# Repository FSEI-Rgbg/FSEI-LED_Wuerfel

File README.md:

# FSEI - LED Würfel - Lötübung

Dieses Projekt wurde als Lötübung ins Leben gerufen. Es handelt sich um eine kleine Platine mit 7 LEDs und einem Taster. Beim Drücken des Tasters wird eine Zahl zwischen 1 und 6 gewürfelt, wie bei einem echten Würfel auch.

## Wie sieht denn der Würfel eigentlich aus?
Bei einem solchen Projekt darf natürlich der FSEIgel nicht fehlen. Er hat selbstverständlich seinen ganz eigenen Platz auf der Platine bekommen.<p>
<p>
<p>
<p>
Eine [interaktive BOM](https://htmlpreview.github.io/?https://github.com/FSEI-Rgbg/FSEI-LED_Wuerfel/blob/main/Hardware%20-%20KiCAD/KiCAD-Project/bom/FSEI_WuerfelPlatine_v2.0.html) zur einfachen Komponentenplatzierung gibt's natürlich auch.

## Projekt Status
Der Würfel ist voll funktionsfähig und als Lötübung in der Fachschaft Elektro- und Informationstechnik als Kit mit allen benötigten Komponenten sowie bereits installierter Software erhältlich.

Still ToDo:
- Version 2.0 ist (Stand 02.07.2023) noch UNTESTED!
- Dokumentation
- Bilder von KIT hinzufügen

## Zielgruppe / Dauer
<p> Diese Lötübung zielt auf alle Elektro- und Lötbegeisterten, oder die die es noch werden möchten, ab einem Alter von etwa 12-14 Jahren ab.
<p>Mit ein wenig handwerklichem Geschick kann nach etwa 30-45 Minuten losgewürfelt werden.

## Kit
**TODO** - _Bild folgt!_
<br>
<p>Der Würfel wird mit allen benötigten Bauteilen in einer kleinen Box herausgegeben. Enthalten ist alles, von der Platine, über die Batterie bis hin zu den LEDs.
<p>Wenn es für dich möglich ist, würden wir dich bitten, die Box nach erfolgreichem Zusammenbau wieder bei uns abzugeben.
<p>Danke für deine Mithilfe.

## Dokumentation
**TODO**
<br>
Eine Dokumentation wie alles funktioniert, zusammengebaut werden muss inkl. einer kurzen Erklärung für alles Weitere findest du [hier](/Doku/Dokumentation-FSEI-LED_Wuerfel_v2.0.pdf).<p>
Der interaktive Bestückungsplan ist [hier](https://htmlpreview.github.io/?https://github.com/FSEI-Rgbg/FSEI-LED_Wuerfel/blob/main/Hardware%20-%20KiCAD/KiCAD-Project/bom/FSEI_WuerfelPlatine_v2.0.html) zu finden. Damit kannst du einfach der Reihe nach alle Komponenten einbauen und Stück für Stück abhaken, was du schon erledigt hast.

## Support
Bei Problemen, Fragen oder Anregungen bitte einfach bei der Fachschaft Elektro- und Informationstechnik (S060) melden.

## Software
**TODO**
<br>
Beim Drücken des Tasters wird ein Timer gestartet, außerdem startet eine Würfelanimation. Beim Loslassen des Tasters wird eine Zufallszahl gewürfelt, dargestellt und nach etwa 7 Sekunden wieder ausgeschalten. Durch die gedrückte Zeit des Tasters ergibt sich hierbei die Zufälligkeit. <p>
Weitere Details findest du in der [Dokumentation](#Dokumentation) oder im [Programmcode](/Software/Code/).

## Hardware
<p>Die Version 1.0 des Würfels wurde mit Hilfe von EasyEDA erstellt. Die Version 2.0 der Platine enthält einige Verbesserungen des ursprünglichen Designs und wurde in KiCAD realisiert.
<p>Im Mittelpunkt der Platine steht neben unserem FSEIgel natürlich ein kleiner Computer, ein sogenannter Mikroprozessor. Wir haben uns hierbei für den ATtiny13A von Atmel entschieden.

## Technische Daten / Stromverbrauch
- Stromaufnahme bei 3V: <p>
Modus  &  Stromaufnahme <p>
0,088 uA  @  Tiefschlafmodus <p>
0,9 mA  @  0 LEDs, CPU Idle <p>
1,808 mA  @  1 LED, CPU Idle <p>
10,8 mA  @  6 LEDs, CPU Idle

- Maße: 60 x 35 x ~10 mm

- Verwendungszweck: Würfel für Spieleabende

## Ich habe einen Bug gefunden oder eine Verbesserung
[Siehe Support](#Support)

## Wir sind ein Verein oder Gruppe von Studenten und wollen mehrere Bausätze kaufen
Es ist toll, dass du anderen Zeigen möchtest wie einfach Löten oder Elektrotechnik sein kann. Melde dich bei uns.

## Autoren
- Leo Scherer
- Patrick Lermer

## Inspired by
BlinkyParts
- https://github.com/Binary-Kitchen/SolderingTutorial
- https://binary-kitchen.github.io/SolderingTutorial/
- https://shop.blinkyparts.com/de/Bausaetze/

## Copyright and Authorship
[CC-BY-SA 4.0](https://creativecommons.org/licenses/by-sa/4.0/) - Fachschaft Elektro- und Informationstechnik der OTH Regensburg

[© FSEI OTH Regensburg](https://www.fsei-regensburg.de)

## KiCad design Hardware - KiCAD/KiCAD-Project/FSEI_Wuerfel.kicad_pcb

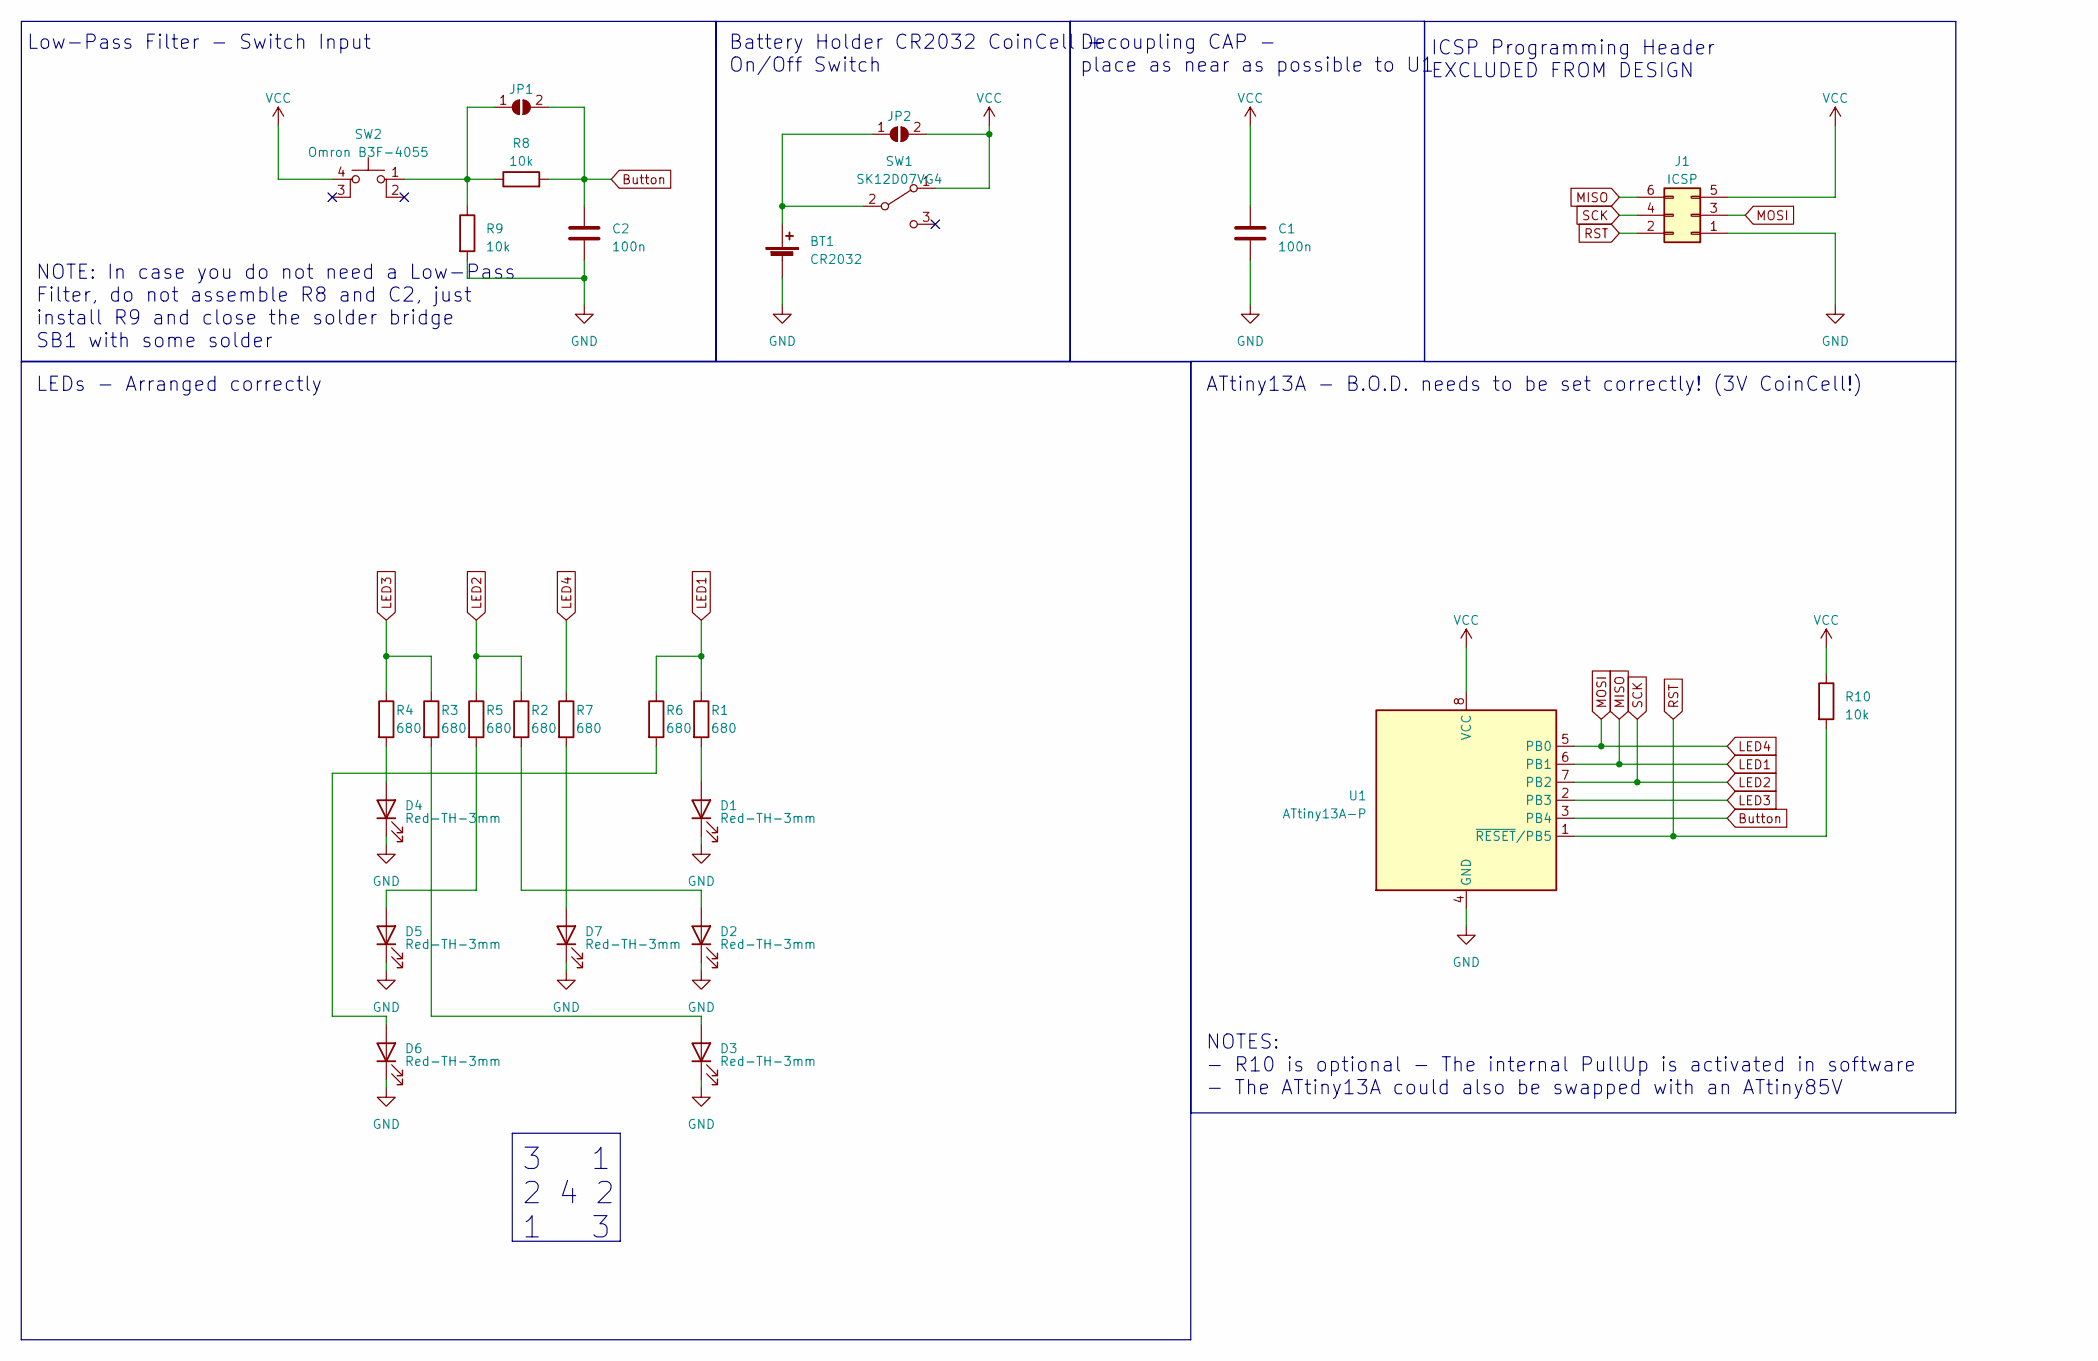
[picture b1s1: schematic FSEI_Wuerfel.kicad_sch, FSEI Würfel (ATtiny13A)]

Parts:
BT1: CR2032; BAT-TH_BS-2-1
C1, C2: 100n; C_Disc_D3.0mm_W1.6mm_P2.50mm
D1, D2, D3, D4, D5, D6, D7: Red-TH-3mm; LED_D3.0mm
J1: ICSP; PinSocket_2x03_P2.54mm_Vertical
JP1, JP2: SolderJumper_2_Open; SolderJumper-2_P1.3mm_Open_RoundedPad1.0x1.5mm
R1, R2, R3, R4, R5, R6, R7: 680; R_Axial_DIN0207_L6.3mm_D2.5mm_P10.16mm_Horizontal
R8, R9, R10: 10k; R_Axial_DIN0207_L6.3mm_D2.5mm_P10.16mm_Horizontal
SW1: SK12D07VG4; SW-TH_SK12D07VG4
SW2: Omron B3F-4055; KEY-TH_4P-L12.0-W12.0-P5.00-LS13.4-EH
U1: ATtiny13A-P; DIP-8_W7.62mm

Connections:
Button: C2.1, JP1.2 (B), R8.2, U1.3 (PB4)
GND: BT1.2 (-), C1.2, C2.2, D1.1 (K), D2.1 (K), D3.1 (K), D4.1 (K), D5.1 (K), D6.1 (K), D7.1 (K), J1.1, R9.2, U1.4 (GND)
LED1: J1.6, R1.1, R6.1, U1.6 (PB1)
LED2: J1.4, R2.1, R5.1, U1.7 (PB2)
LED3: R3.1, R4.1, U1.2 (PB3)
LED4: J1.3, R7.1, U1.5 (PB0)
unnamed: BT1.1 (+), JP2.1 (A), SW1.2 (B)
unnamed: D1.2 (A), R1.2
unnamed: D2.2 (A), R2.2
unnamed: D3.2 (A), R3.2
unnamed: D4.2 (A), R4.2
unnamed: D5.2 (A), R5.2
unnamed: D6.2 (A), R6.2
unnamed: D7.2 (A), R7.2
unnamed: JP1.1 (A), R8.1, R9.1, SW2.1
RST: J1.2, R10.2, U1.1 (~RESET/PB5)
VCC: C1.1, J1.5, JP2.2 (B), R10.1, SW1.1 (A), SW2.4 (A), U1.8 (VCC)

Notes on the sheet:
3 1 2 4 2 1 3
ICSP Programming Header EXCLUDED FROM DESIGN
NOTE: In case you do not need a Low-Pass Filter, do not assemble R8 and C2, just install R9 and close the solder bridge SB1 with some solder
Decoupling CAP - place as near as possible to U1
Low-Pass Filter - Switch Input
NOTES: - R10 is optional - The internal PullUp is activated in software - The ATtiny13A could also be swapped with an ATtiny85V
ATtiny13A - B.O.D. needs to be set correctly! (3V CoinCell!)
Battery Holder CR2032 CoinCell + On/Off Switch
LEDs - Arranged correctly

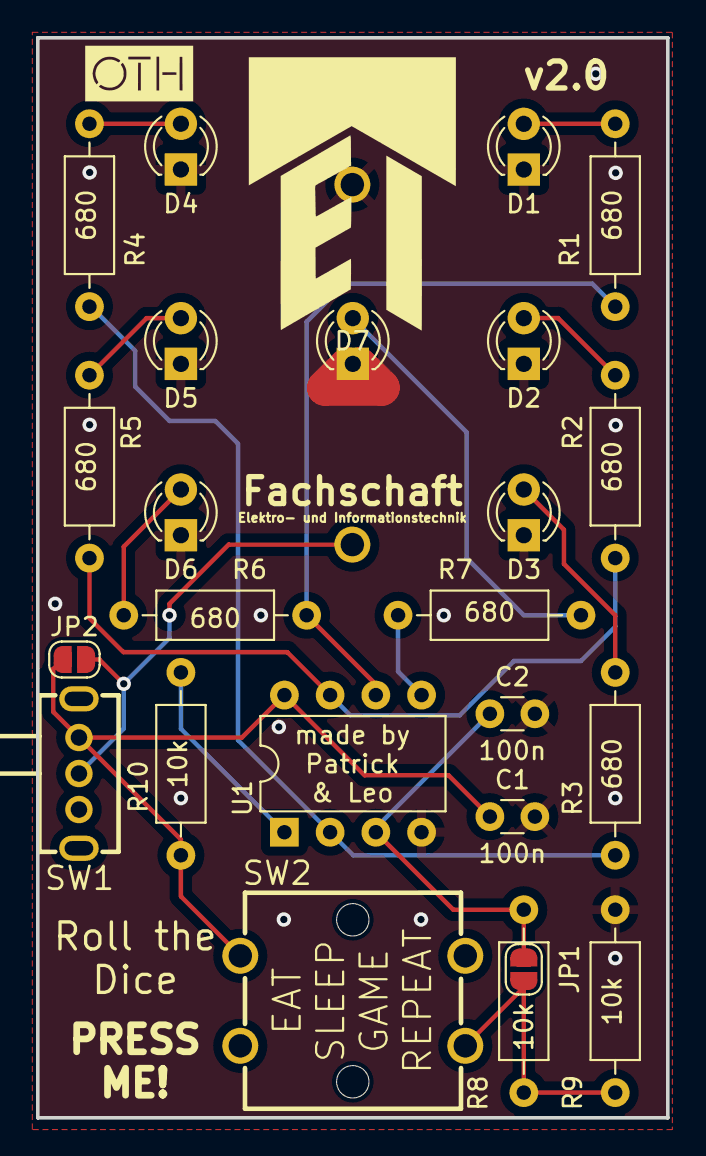
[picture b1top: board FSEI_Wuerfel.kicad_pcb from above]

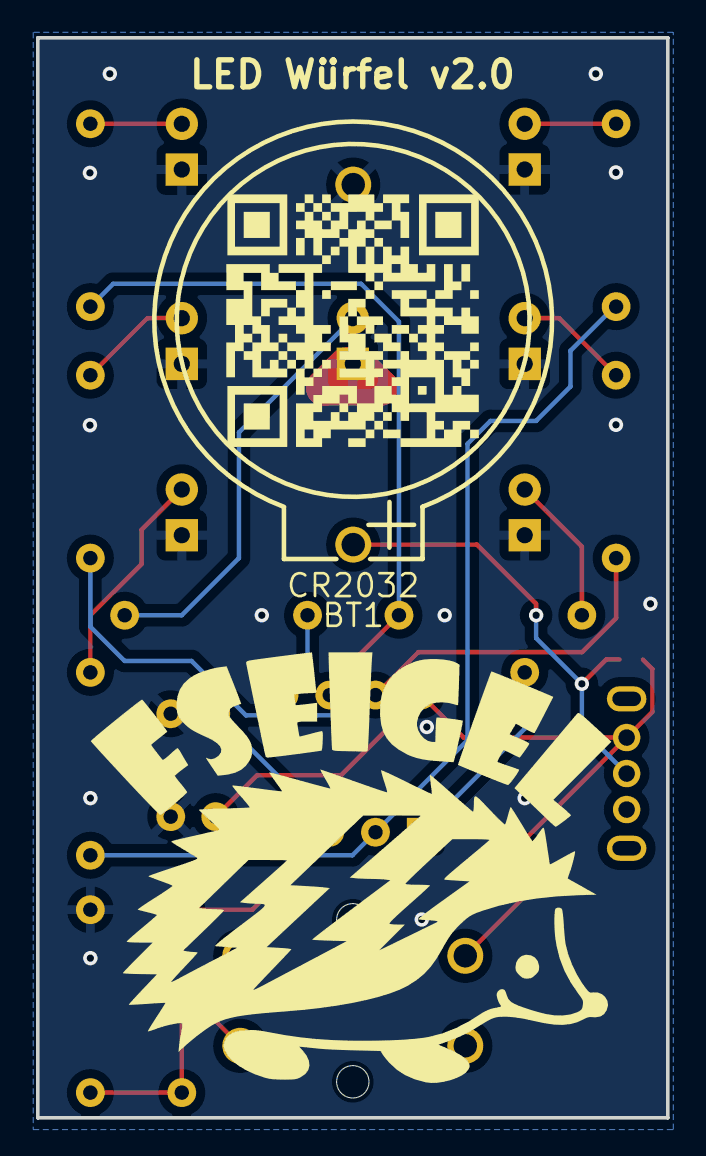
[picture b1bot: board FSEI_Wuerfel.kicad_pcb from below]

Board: 2 copper layers, 35.0 x 60.0 mm, 30 parts (3 on the bottom side), 17 nets.

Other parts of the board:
G01, G02, G011, G012, G100: LOGO

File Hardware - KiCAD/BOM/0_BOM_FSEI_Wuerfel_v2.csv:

"Source:","C:\Users\Patrick\OneDrive\Dokumente\FSEI\FSEI-LED_Wuerfel\Hardware - KiCAD\KiCAD-Project\FSEI_Wuerfel.kicad_sch"
"Date:","6/22/2023 8:53:04 AM"
"Tool:","Eeschema 7.0.2"
"Generator:","C:\Program Files\KiCad\7.0\bin\scripting\plugins/bom_csv_grouped_by_value_with_fp.py"
"Component Count:","25"
"Ref","Qnty","Value","Cmp name","Footprint","Description","Vendor","DNP"
"BT1","1","CR2032","Battery_Cell","C70376:BAT-TH_BS-2-1","Single-cell battery","",""
"C1, C2","2","100n","C","Capacitor_THT:C_Disc_D3.0mm_W1.6mm_P2.50mm","Unpolarized capacitor","",""
"D1, D2, D3, D4, D5, D6, D7","7","Red-TH-3mm","LED","LED_THT:LED_D3.0mm","Light emitting diode","",""
"JP1, JP2","2","SolderJumper_2_Open","SolderJumper_2_Open","Jumper:SolderJumper-2_P1.3mm_Open_RoundedPad1.0x1.5mm","Solder Jumper, 2-pole, open","",""
"R1, R2, R3, R4, R5, R6, R7","7","680","R","Resistor_THT:R_Axial_DIN0207_L6.3mm_D2.5mm_P10.16mm_Horizontal","Resistor","",""
"R8, R9, R10","3","10k","R","Resistor_THT:R_Axial_DIN0207_L6.3mm_D2.5mm_P10.16mm_Horizontal","Resistor","",""
"SW1","1","SK12D07VG4","SW_SPDT","C393937:SW-TH_SK12D07VG4","Switch, single pole double throw","",""
"SW2","1","Omron B3F-4055","SW_MEC_5E","C84931:KEY-TH_4P-L12.0-W12.0-P5.00-LS13.4-EH","MEC 5E single pole normally-open tactile switch","",""
"U1","1","ATtiny13A-P","ATtiny13A-P","Package_DIP:DIP-8_W7.62mm","20MHz, 1kB Flash, 64B SRAM, 64B EEPROM, debugWIRE, DIP-8","",""

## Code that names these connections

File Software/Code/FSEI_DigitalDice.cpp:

/*
Fachschaft Elektro- & Informationstechnik, OTH Regensburg, ©2023

Digitaler Würfel - Lötübung
ATtiny13A oder ATtiny85V

Inputs:    
    Taster mit PullDown und LowPassFilter an PB4 (Pin 3) - Interrupt PCINT4

Outputs:   
    LED Gruppen:
        LED1 = PB1 (Pin 6)
        LED2 = PB2 (Pin 7)
        LED3 = PB3 (Pin 2)
        LED4 = PB0 (Pin 5)
    ┌───┐   ┌───┐
    │ 3 │   │ 1 │
    ├───┼───┼───┤
    │ 2 │ 4 │ 2 │
    ├───┼───┼───┤
    │ 1 │   │ 3 │
    └───┘   └───┘

Funktionsprinzip:
    uC geht direkt in Tiefschlafmodus um Strom zu sparen.
    Sobald der Taster gedrückt wird, aktiviert sich der Timer (der mit 9,6MHz zählt), 
    und zählt endlos nach oben und läuft über. Die CPU ist dabei Idle.
    Sobald der Taster losgelassen wird, wird per XOR und Modulo aus dem Wert des Timers die anzuzeigende Zahl bestimmt.
    Dann wird der Interrupt des Timers aktiviert, welcher den TIMER_COUNTER solange hochzählt, 
    bis etwa 7s vergangen sind. Dann wird alles deaktiviert und wieder in den Tiefschlafmodus versetzt.

Stromaufnahme bei 3V:
    Tiefschlafmodus:    0,088 uA
    0 LEDs, CPU Idle:     0,9 mA
    1 LED, CPU Idle:    1,808 mA
    6 LEDs, CPU Idle:    10,8 mA
*/

// Einbinden aller benötigten Bibliotheken (Zusatzfunktionen)
#include <avr/io.h>
#include <avr/interrupt.h>
#include <avr/sleep.h>

// Timer Modus für das Warten auf Abschaltung, dadurch hat er einen hohen Prescaler und wenig Interrupts.
#define TMODE_IDLE 0
// Timer Modus für das Ermitteln einer Zufallszahl, dafür wird die höchste Auflösung und kein Prescaler benötigt.
#define TMODE_TRNG 1


// Zusätzlicher Zähler, um den Timer auf 24-Bit zu erweitern.
volatile unsigned short TIMER_COUNTER = 0;
// Timer Modus Variable, die den derzeitigen Zustand speichert.
volatile unsigned char TIMER_USAGE_MODE = 0;
// Zähler für das Durchlaufen aller Würfelzustände
volatile unsigned char DICE_ANIM_COUNTER = 0;
// Speicher für den vorherigen Würfel-Wurf.
volatile unsigned char PREV_DICE_ROLL = 0;


// Ausgabe der gewürfelten Augenzahl auf LEDs. Rest von PORTB bleibt unverändert.
void DisplayAugenzahl(unsigned char Zahl)     
{
    // Alle LEDs deaktivieren
    PORTB &= ~((1 << PORTB3) | (1 << PORTB2) | (1 << PORTB1) | (1 << PORTB0));

    switch (Zahl)
    {
        case 1: //LED4
            PORTB |= (1 << PORTB0);
        break;

        case 2: // LED1
            PORTB |= (1 << PORTB1);
            break;

        case 3: // LED1 & LED4
            PORTB |= ((1 << PORTB1) | (1 << PORTB0));
            break;

        case 4: // LED1 & LED3
            PORTB |= ((1 << PORTB1) | (1 << PORTB3));
            break;

        case 5: // LED1 & LED3 & LED4
            PORTB |= ((1 << PORTB1) | (1 << PORTB3) | (1 << PORTB0));
            break;

        case 6: // LED1 & LED2 & LED3
            PORTB |= ((1 << PORTB1) | (1 << PORTB2) | (1 << PORTB3));
            break;

        default: 
            break;
    }
}


// Timer im jeweiligen Modus aktivieren und mit einem festgelegten Wert starten.
void activate_timer(unsigned char timer_mode, unsigned char timer_value)
{
    TCCR0B = 0x00;                              // Timer stoppen falls er schon läuft.
    TIMER_USAGE_MODE = timer_mode;              // Timer Modus für Interrupt Routine speichern.
    TIMER_COUNTER = 0;                          // Zusätzlichen Timer Counter zurücksetzen.
    TCNT0 = timer_value;                        // Timer Wert setzen.

    TIMSK0 = (1 << TOIE0);                      // Timer-Interrupt anschalten.

    switch (timer_mode)
    {
        case TMODE_IDLE:
            TCCR0B = ((1 << CS02) | (1 << CS00));// Timer anschalten mit Prescaler 1024.
            break;
        case TMODE_TRNG:
            TCCR0B = (1 << CS00);               // Timer ohne Prescaler anschalten.
            break;
        default:                                // etwas ist falsch, timer nicht starten.
            break;
    }
}


// Interrupt Service Routine (ISR) für Flankenwechsel des Tasters. Pin 4 ist High wenn dieser gedrückt wird.
ISR(PCINT0_vect)
{
    if (PINB & (1 << PINB4))                    // Eingang PIN4 abfragen: Taster gedrückt -> Steigende Flanke
    {
        DICE_ANIM_COUNTER = 0;                  // Animations-Zähler für Zwischenanimation zurücksetzen

        activate_timer(TMODE_TRNG, PREV_DICE_ROLL); // Aktiviere den Timer im Zufallszahlen-Modus

        set_sleep_mode(SLEEP_MODE_IDLE);        // Sleep Mode zu nur Idle ändern, damit die Oszillatoren an bleiben und der Timer zählen kann.
    }
    else                                        // Taster nicht gedrückt -> Fallende Flanke
    {
        PREV_DICE_ROLL ^= TCNT0;                // Alten Timer Wert mit neuem Wert XORen für eine bessere Gleichverteilung der Werte und speichern.

        DisplayAugenzahl((PREV_DICE_ROLL % 6) + 1);  // Zufallsgenerierte Zahl aus Timer Wert berechnen und anzeigen.

        activate_timer(TMODE_IDLE, 0);          // Aktiviere den Timer für die Idle-Abschaltung
    }
}

// Interrupt Service Routine (ISR) für den Overflow des Timers. Wird alle 1 / 9,6 MHz * Prescaler * 255 Sekunden aufgerufen.
// Der Prescaler ist 1 im TMODE_TRNG und 1024 im TMODE_IDLE.
ISR(TIM0_OVF_vect)                              
{                                               

    TIMER_COUNTER += 1;                         // TIMER_COUNTER hochzählen. Dient als Erweiterung für den 8-Bit Counter.

    if (TIMER_USAGE_MODE == TMODE_IDLE)         // Wenn der Timer für die Idle-Abschaltung nach zu langer Zeit verwendet wird:
    {
        if (TIMER_COUNTER >= 255)               // Überprüfe ob etwa 7 Sekunden vergangen sind. Falls ja, System für den Tiefschlaf vorbereiten:
        {            
            TCCR0B = 0x00;                      // Timer stoppen.
            TIMSK0 = 0x00;                      // Timer-Interrupt ausschalten.
            DisplayAugenzahl(0);                // Alle LEDs ausschalten.
            set_sleep_mode(SLEEP_MODE_PWR_DOWN);// Sleep Mode zu kompletten Tiefschalf ändern. nach der ISR wird durch die while Schleife in main der Schlaf gestartet.
        }
    }
    else if (TIMER_USAGE_MODE == TMODE_TRNG)    // Wenn der Timer für die Zufallszahlengenerierung verwendet wird:
    {
        if (TIMER_COUNTER >= 6300)              // Überprüfe ob etwa 1/6 einer Sekunde vergangen ist.
        {
            DICE_ANIM_COUNTER += 1;             // Animations-Counter zum Anzeigen eines "hochzählenden" Würfels zurücksetzen.
            DisplayAugenzahl(DICE_ANIM_COUNTER % 6 + 1);    // Zahl anzeigen.
            TIMER_COUNTER = 0;                  // Timer zurücksetzen.
        }
    }
}


int main() 
{ 
    // Interrupts deaktivieren & initialisieren
    cli();   

    // Definieren der PB0-PB3 Outputs, PB4 Input, PB5 Input
    DDRB = ((1 << DDB3) | (1 << DDB2) | (1 << DDB1) | (1 << DDB0));

    // Vorrübergehend: Pull-Up auf Reset Pin aktivieren. Eigentlich ist PB5 durch R10 auf High gezogen.
    PORTB |= (1 << PORTB5);

    // Timer auf Normal Mode stellen (ist normalerweise default)
    TCCR0A = 0x00;

    // Setzen aller Register für Pin Change Interrupt PCINT4
    PCMSK = (1 << PCINT4);  // Pin Change Interrupt für Pin 4 demaskieren
    GIMSK |= (1 << PCIE);   // Pin Change Interrupt aktivieren
    
    // ADC Modul deaktiveren um Strom zu sparen.
    PRR = (1 << PRADC);

    // Tiefschalfmodus als Schlafmodus setzen. 
    set_sleep_mode(SLEEP_MODE_PWR_DOWN); 
    
    // Interrupts aktivieren
    sei();          

    // Endlos schlafen gehen sobald er wieder aufwacht.
    do
    {
        sleep_mode();
    } while(1);
}

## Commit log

2023-07-02 README modified
2023-07-03 added interactive BOM
2023-07-03 fixed link
2023-07-12 README modified and added new binary
